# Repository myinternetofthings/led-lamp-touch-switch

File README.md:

# Led lamp dimmer with touch buttons
Led lamp controller with touch dimmer function.
There are 2 touch buttons that increase and decrease brightness. Brightness is controller via PWM output using power mosfet.
Dimming function has 128 levels mapped via exponential function to 10bits of PWM.
Pressing any button for less than about 0.5s turns lamp off. Pressing any button again turns lamp on with previous brightness level saved.

Project is developed in MPLAB X IDE v3.51.
Microcontroller used is Microchip PIC16F1823.
Unfortunately mtouch library consumed almost all resources, and I had to manually optimize it. Side effect is that MPLAB Code Configurator can no longer automatically merge changes made in gui. 
It would be better to get microcontroller with 2 times more memory, but it's just what I had in my parts bin.

## PCB and schematic
There is small board prepared, and sent to manufacturing by itead.cc.
Schematic, and board was drew in Eagle. Files are in pcb folder.
Production files are prepared in Prototype1.zip.

Boards were manufactured in cheap prototyping pool in ITEAD.cc
Here is a board assembled with dummy load connected:

Main tasks were completed, but this is still work in progress.

## Code statistics
Compiled with free version of xc8 v1.40
- data: 100/128 bytes used (78%)
- code: 1988/2048 words used (97%)

## Next tasks:
- [x] optimize libraries further to make more place for application code.
- [x] add quick on/off function (right now brightness can be lowered to 0)
- [x] add schematic, and design PCB
- [ ] mount to bed with hidden touch buttons, and connect IKEA led lamps

## Fail 1 - lesson learned
When I ran prototype at high power, transistor drain pins were getting extremely hot - I measured 50 C over ambient temperature.
I immediately blamed power transistor losses, because I used different type than in breadboard prototype. After trying 3 other power transistors from my scrap bin, and thinking about better gate drive, and attaching heat sink I spotted that R5 is 100 ohm instead of 100kOhm.
First I thought that these are switching losses. I checked if transistor is turning on correctly, and it seemed fine. Just to be sure I lowered gate resistor to 11 Ohm.
Then I correlated temperature rise with power output, and checked Rds_on (indirectly by measuring Vds with oscillosope, and looking on average current on power supply). This also looked ok.
I lost couple hours before I noticed incorrect resistor value. It also helped to notice that the transistor case was unporportionaly colder than it should be at that high drain leads temperature. Probably source leads were sinking enough heat to keep plastic case cool.

After all that I rised gate resistor back to 47 Ohms to prevent microcontroller output latchup (it's already quite stressed - peak current when turning on is around 100mA for 80ns).

Here are Vd rise and fall waveforms:

Vg gate waveforms:

This is Vd, and I can't quite explain slow rise after turn off - possibly it's capacitance in LEDs.

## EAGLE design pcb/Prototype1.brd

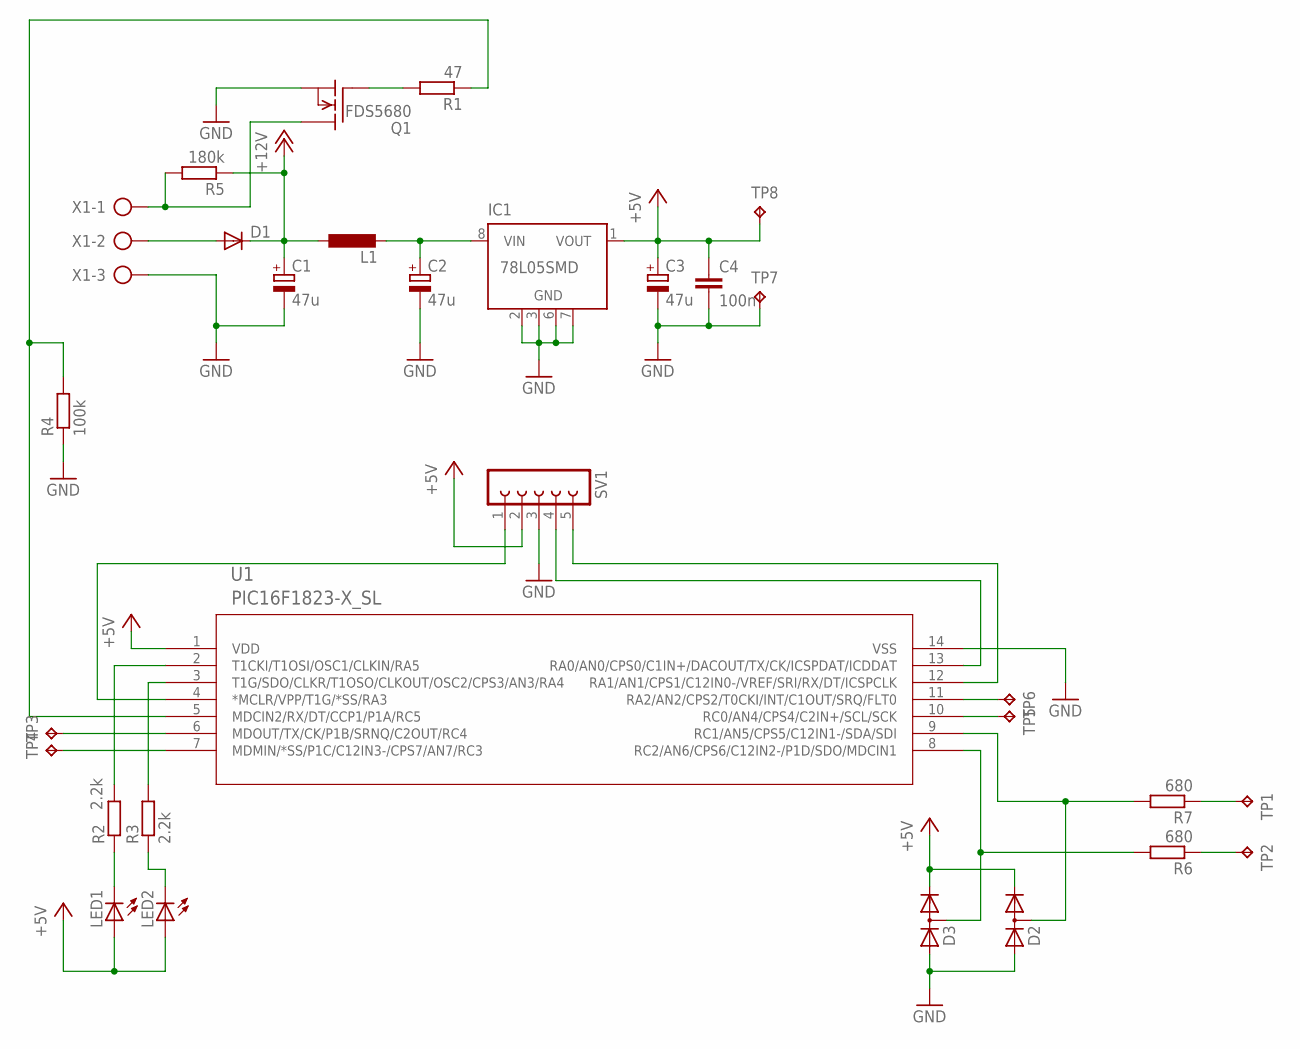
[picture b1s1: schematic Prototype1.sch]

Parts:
C1, C2, C3: 47u; 153CLV-0605
C4: 100n; C0805
D1: DIODE-MELF-MLL41; MELF-MLL41
D2, D3: DIODE_2CACA-SOT23; SOT23
IC1: 78L05SMD; SO08
L1: L-EUL3230M; L3230M
LED1, LED2: LEDSML1206; SML1206
Q1: FDS5680; SO-8
R1: 47; M1206
R2, R3: 2.2k; M1206
R4: 100k; M1206
R5: 180k; M1206
R6, R7: 680; M1206
SV1: FE05-1
TP1, TP2: TPPAD1-13Y; P1-13Y
TP3, TP4, TP5, TP6, TP7, TP8: TPB2,54; B2,54
U1: PIC16F1823-X_SL; SOIC14-N_MC
X1: AK500/3

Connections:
+5V: C3.+, C4.1, D2.2 (C), D3.2 (C), IC1.1 (VOUT), LED1.A, LED2.A, SV1.2, TP8.TP, U1.1 (VDD)
+12V: C1.+, D1.C, L1.1, R5.1
GND: C1.-, C2.-, C3.-, C4.2, D2.1 (A), D3.1 (A), IC1.2 (GND), IC1.3 (GND), IC1.6 (GND), IC1.7 (GND), Q1.1 (S), Q1.2 (S), Q1.3 (S), R4.1, SV1.3, TP7.TP, U1.14 (VSS), X1.3
unnamed: D1.A, X1.2
unnamed: C2.+, IC1.8 (VIN), L1.2
unnamed: Q1.5 (D), Q1.6 (D), Q1.7 (D), Q1.8 (D), R5.2, X1.1
unnamed: Q1.4 (G), R1.2
unnamed: D3.3 (AC), R6.2, U1.8 (RC2/AN6/CPS6/C12IN2-/P1D/SDO/MDCIN1)
unnamed: D2.3 (AC), R7.2, U1.9 (RC1/AN5/CPS5/C12IN1-/SDA/SDI)
unnamed: SV1.4, U1.13 (RA0/AN0/CPS0/C1IN+/DACOUT/TX/CK/ICSPDAT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)
unnamed: SV1.5, U1.12 (RA1/AN1/CPS1/C12IN0-/VREF/SRI/RX/DT/ICS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)
unnamed: SV1.1, U1.4 (*MCLR/VPP/T1G/*SS/RA3)
unnamed: R1.1, R4.2, U1.5 (MDCIN2/RX/DT/CCP1/P1A/RC5)
unnamed: R7.1, TP1.TP
unnamed: R6.1, TP2.TP
unnamed: LED2.C, R3.1
unnamed: LED1.C, R2.1
unnamed: R3.2, U1.3 (T1G/SDO/CLKR/T1OSO/CLKOUT/OSC2/CPS3/AN3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)
unnamed: R2.2, U1.2 (T1CKI/T1OSI/OSC1/CLKIN/RA5)
unnamed: TP3.TP, U1.6 (MDOUT/TX/CK/P1B/SRNQ/C2OUT/RC4)
unnamed: TP4.TP, U1.7 (MDMIN/*SS/P1C/C12IN3-/CPS7/AN7/RC3)
unnamed: TP5.TP, U1.10 (RC0/AN4/CPS4/C2IN+/SCL/SCK)
unnamed: TP6.TP, U1.11 (RA2/AN2/CPS2/T0CKI/INT/C1OUT/SRQ/FLT0)

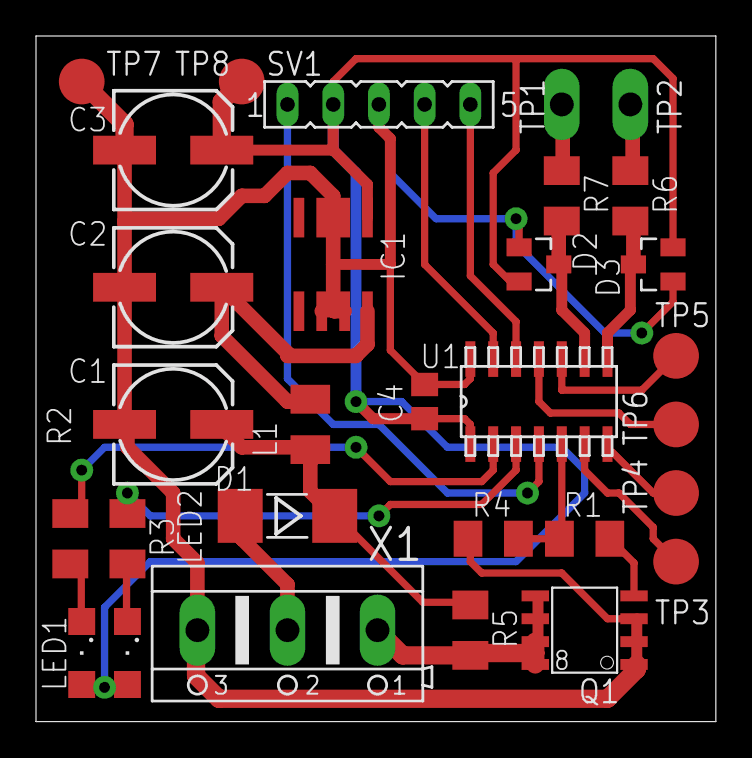
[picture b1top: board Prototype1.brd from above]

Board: 2 copper layers, 37.8 x 38.1 mm, 30 parts (0 on the bottom side), 23 nets.

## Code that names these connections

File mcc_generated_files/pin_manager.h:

/**
  @Generated Pin Manager Header File

  @Company:
    Microchip Technology Inc.

  @File Name:
    pin_manager.h

  @Summary:
    This is the Pin Manager file generated using MPLAB(c) Code Configurator

  @Description:
    This header file provides implementations for pin APIs for all pins selected in the GUI.
    Generation Information :
        Product Revision  :  MPLAB(c) Code Configurator - 4.15
        Device            :  PIC16F1823
        Version           :  1.01
    The generated drivers are tested against the following:
        Compiler          :  XC8 1.35
        MPLAB             :  MPLAB X 3.40

    Copyright (c) 2013 - 2015 released Microchip Technology Inc.  All rights reserved.

    Microchip licenses to you the right to use, modify, copy and distribute
    Software only when embedded on a Microchip microcontroller or digital signal
    controller that is integrated into your product or third party product
    (pursuant to the sublicense terms in the accompanying license agreement).

    You should refer to the license agreement accompanying this Software for
    additional information regarding your rights and obligations.

    SOFTWARE AND DOCUMENTATION ARE PROVIDED "AS IS" WITHOUT WARRANTY OF ANY KIND,
    EITHER EXPRESS OR IMPLIED, INCLUDING WITHOUT LIMITATION, ANY WARRANTY OF
    MERCHANTABILITY, TITLE, NON-INFRINGEMENT AND FITNESS FOR A PARTICULAR PURPOSE.
    IN NO EVENT SHALL MICROCHIP OR ITS LICENSORS BE LIABLE OR OBLIGATED UNDER
    CONTRACT, NEGLIGENCE, STRICT LIABILITY, CONTRIBUTION, BREACH OF WARRANTY, OR
    OTHER LEGAL EQUITABLE THEORY ANY DIRECT OR INDIRECT DAMAGES OR EXPENSES
    INCLUDING BUT NOT LIMITED TO ANY INCIDENTAL, SPECIAL, INDIRECT, PUNITIVE OR
    CONSEQUENTIAL DAMAGES, LOST PROFITS OR LOST DATA, COST OF PROCUREMENT OF
    SUBSTITUTE GOODS, TECHNOLOGY, SERVICES, OR ANY CLAIMS BY THIRD PARTIES
    (INCLUDING BUT NOT LIMITED TO ANY DEFENSE THEREOF), OR OTHER SIMILAR COSTS.

*/


#ifndef PIN_MANAGER_H
#define PIN_MANAGER_H

#define INPUT   1
#define OUTPUT  0

#define HIGH    1
#define LOW     0

#define ANALOG      1
#define DIGITAL     0

#define PULL_UP_ENABLED      1
#define PULL_UP_DISABLED     0

// get/set Led2 aliases
#define Led2_TRIS               TRISAbits.TRISA4
#define Led2_LAT                LATAbits.LATA4
#define Led2_PORT               PORTAbits.RA4
#define Led2_WPU                WPUAbits.WPUA4
#define Led2_ANS                ANSELAbits.ANSA4
#define Led2_SetHigh()            do { LATAbits.LATA4 = 1; } while(0)
#define Led2_SetLow()             do { LATAbits.LATA4 = 0; } while(0)
#define Led2_Toggle()             do { LATAbits.LATA4 = ~LATAbits.LATA4; } while(0)
#define Led2_GetValue()           PORTAbits.RA4
#define Led2_SetDigitalInput()    do { TRISAbits.TRISA4 = 1; } while(0)
#define Led2_SetDigitalOutput()   do { TRISAbits.TRISA4 = 0; } while(0)
#define Led2_SetPullup()      do { WPUAbits.WPUA4 = 1; } while(0)
#define Led2_ResetPullup()    do { WPUAbits.WPUA4 = 0; } while(0)
#define Led2_SetAnalogMode()  do { ANSELAbits.ANSA4 = 1; } while(0)
#define Led2_SetDigitalMode() do { ANSELAbits.ANSA4 = 0; } while(0)

// get/set Led1 aliases
#define Led1_TRIS               TRISAbits.TRISA5
#define Led1_LAT                LATAbits.LATA5
#define Led1_PORT               PORTAbits.RA5
#define Led1_WPU                WPUAbits.WPUA5
#define Led1_SetHigh()            do { LATAbits.LATA5 = 1; } while(0)
#define Led1_SetLow()             do { LATAbits.LATA5 = 0; } while(0)
#define Led1_Toggle()             do { LATAbits.LATA5 = ~LATAbits.LATA5; } while(0)
#define Led1_GetValue()           PORTAbits.RA5
#define Led1_SetDigitalInput()    do { TRISAbits.TRISA5 = 1; } while(0)
#define Led1_SetDigitalOutput()   do { TRISAbits.TRISA5 = 0; } while(0)
#define Led1_SetPullup()      do { WPUAbits.WPUA5 = 1; } while(0)
#define Led1_ResetPullup()    do { WPUAbits.WPUA5 = 0; } while(0)

// get/set Input1 aliases
#define Input1_TRIS               TRISCbits.TRISC0
#define Input1_LAT                LATCbits.LATC0
#define Input1_PORT               PORTCbits.RC0
#define Input1_WPU                WPUCbits.WPUC0
#define Input1_ANS                ANSELCbits.ANSC0
#define Input1_SetHigh()            do { LATCbits.LATC0 = 1; } while(0)
#define Input1_SetLow()             do { LATCbits.LATC0 = 0; } while(0)
#define Input1_Toggle()             do { LATCbits.LATC0 = ~LATCbits.LATC0; } while(0)
#define Input1_GetValue()           PORTCbits.RC0
#define Input1_SetDigitalInput()    do { TRISCbits.TRISC0 = 1; } while(0)
#define Input1_SetDigitalOutput()   do { TRISCbits.TRISC0 = 0; } while(0)
#define Input1_SetPullup()      do { WPUCbits.WPUC0 = 1; } while(0)
#define Input1_ResetPullup()    do { WPUCbits.WPUC0 = 0; } while(0)
#define Input1_SetAnalogMode()  do { ANSELCbits.ANSC0 = 1; } while(0)
#define Input1_SetDigitalMode() do { ANSELCbits.ANSC0 = 0; } while(0)

// get/set RC1 procedures
#define RC1_SetHigh()    do { LATCbits.LATC1 = 1; } while(0)
#define RC1_SetLow()   do { LATCbits.LATC1 = 0; } while(0)
#define RC1_Toggle()   do { LATCbits.LATC1 = ~LATCbits.LATC1; } while(0)
#define RC1_GetValue()         PORTCbits.RC1
#define RC1_SetDigitalInput()   do { TRISCbits.TRISC1 = 1; } while(0)
#define RC1_SetDigitalOutput()  do { TRISCbits.TRISC1 = 0; } while(0)
#define RC1_SetPullup()     do { WPUCbits.WPUC1 = 1; } while(0)
#define RC1_ResetPullup()   do { WPUCbits.WPUC1 = 0; } while(0)
#define RC1_SetAnalogMode() do { ANSELCbits.ANSC1 = 1; } while(0)
#define RC1_SetDigitalMode()do { ANSELCbits.ANSC1 = 0; } while(0)

// get/set RC2 procedures
#define RC2_SetHigh()    do { LATCbits.LATC2 = 1; } while(0)
#define RC2_SetLow()   do { LATCbits.LATC2 = 0; } while(0)
#define RC2_Toggle()   do { LATCbits.LATC2 = ~LATCbits.LATC2; } while(0)
#define RC2_GetValue()         PORTCbits.RC2
#define RC2_SetDigitalInput()   do { TRISCbits.TRISC2 = 1; } while(0)
#define RC2_SetDigitalOutput()  do { TRISCbits.TRISC2 = 0; } while(0)
#define RC2_SetPullup()     do { WPUCbits.WPUC2 = 1; } while(0)
#define RC2_ResetPullup()   do { WPUCbits.WPUC2 = 0; } while(0)
#define RC2_SetAnalogMode() do { ANSELCbits.ANSC2 = 1; } while(0)
#define RC2_SetDigitalMode()do { ANSELCbits.ANSC2 = 0; } while(0)

// get/set RC5 procedures
#define RC5_SetHigh()    do { LATCbits.LATC5 = 1; } while(0)
#define RC5_SetLow()   do { LATCbits.LATC5 = 0; } while(0)
#define RC5_Toggle()   do { LATCbits.LATC5 = ~LATCbits.LATC5; } while(0)
#define RC5_GetValue()         PORTCbits.RC5
#define RC5_SetDigitalInput()   do { TRISCbits.TRISC5 = 1; } while(0)
#define RC5_SetDigitalOutput()  do { TRISCbits.TRISC5 = 0; } while(0)
#define RC5_SetPullup()     do { WPUCbits.WPUC5 = 1; } while(0)
#define RC5_ResetPullup()   do { WPUCbits.WPUC5 = 0; } while(0)

#define LedEn_SetHigh()            do { LATCbits. LATC4 = 1; } while(0)
#define LedEn_SetLow()             do { LATCbits.LATC4 = 0; } while(0)
/**
   @Param
    none
   @Returns
    none
   @Description
    GPIO and peripheral I/O initialization
   @Example
    PIN_MANAGER_Initialize();
 */
void PIN_MANAGER_Initialize (void);

/**
 * @Param
    none
 * @Returns
    none
 * @Description
    Interrupt on Change Handling routine
 * @Example
    PIN_MANAGER_IOC();
 */
void PIN_MANAGER_IOC(void);



#endif // PIN_MANAGER_H
/**
 End of File
*/

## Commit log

2017-02-12 initial import
2017-02-13 further code optimizations and cleanup 96 words available
2017-02-14 Added on/off - short press and release turns lamp off Added tick synchronized section Lamp is off after power on
2017-04-05 Added PCB
2017-07-16 Fixed reversed lampOn compare ticks, and pressTicks extended to 16 bits adjusted short press time for lamp on/off
2017-07-16 Updated readme after assembling boards added assembled board pictures
2017-07-18 Added waveforms, added component values to schematic. Added fail description, and lesson learned to readme.
2017-07-18 Updated gitignore
2017-07-18 Spelling, and images corrected
2017-07-18 Formatting corrected
2018-03-13 added enable pin control (active high). Added stl for led bar from 14" LCD backlight.
